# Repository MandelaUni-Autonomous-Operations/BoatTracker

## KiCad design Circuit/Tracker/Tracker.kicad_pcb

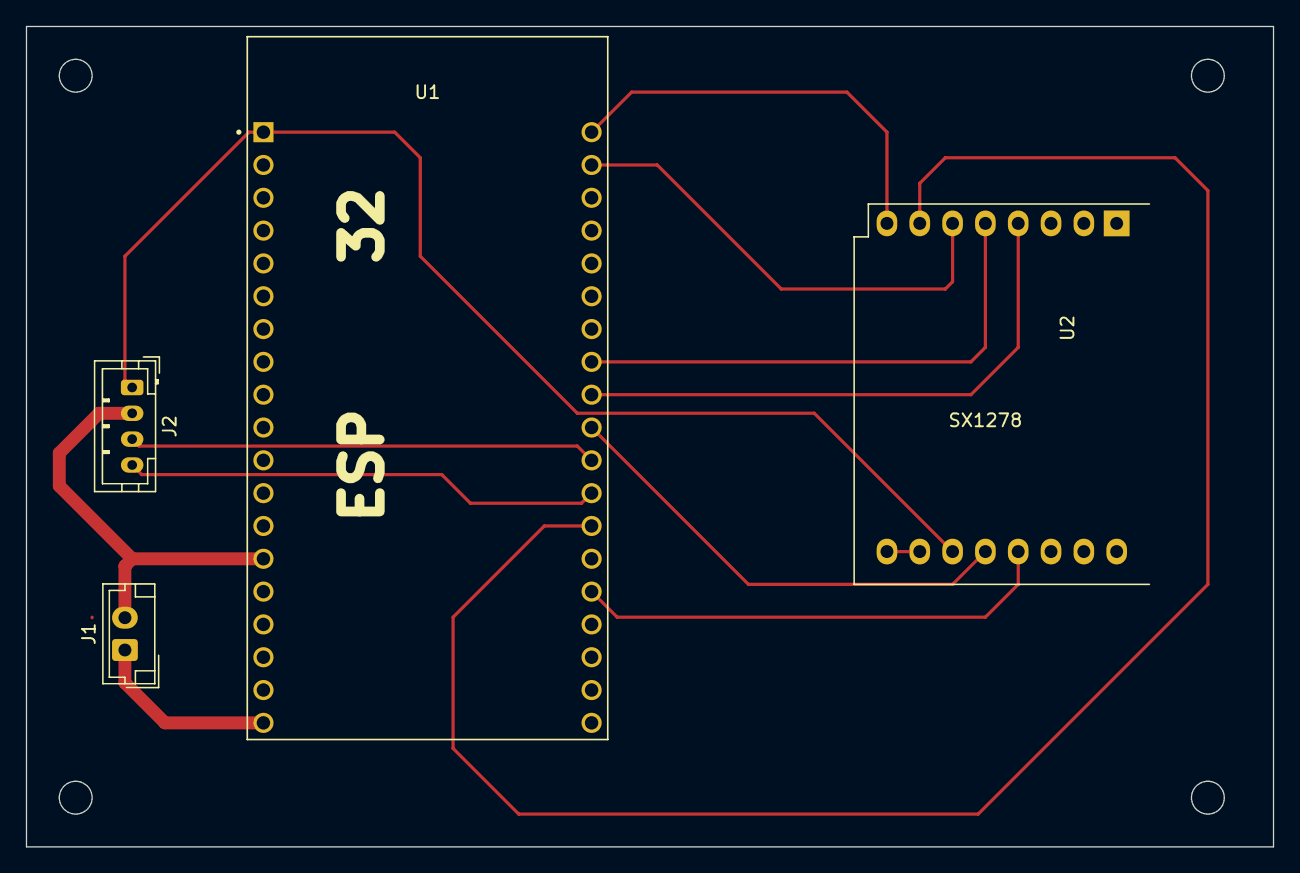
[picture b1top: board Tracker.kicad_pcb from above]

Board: 2 copper layers, 96.5 x 63.5 mm, 4 parts (0 on the bottom side), 11 nets.

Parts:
J1: Conn_01x02_Female; JST_EH_B2B-EH-A_1x02_P2.50mm_Vertical
J2: Conn_01x04_Female; JST_PH_B4B-PH-K_1x04_P2.00mm_Vertical
U1: ESP32-DEVKITC-32D; MODULE_ESP32-DEVKITC-32D
U2: SX1278; SX1276 Module

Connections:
GND: J1.2, J2.2, U1.J2-14 (GND1), U1.J3-1 (GND3), U1.J3-7 (GND2), U2.2 (VR_ANA), U2.4 (VR_DIG), U2.15 (GND)
unnamed: J1.1, U1.J2-19 (EXT_5V)
unnamed: J2.1, U1.J2-1 (3V3), U2.14 (VBAT_DIG)
unnamed: J2.3, U1.J3-11 (IO17)
unnamed: J2.4, U1.J3-12 (IO16)
unnamed: U1.J3-2 (IO23), U2.18 (MOSI)
unnamed: U1.J3-8 (IO19), U2.17 (MISO)
unnamed: U1.J3-9 (IO18), U2.16 (SCK)
unnamed: U1.J3-10 (IO5), U2.7 (~RESET)
unnamed: U1.J3-13 (IO4), U2.19 (NSS)
unnamed: U1.J3-15 (IO2), U2.8 (DIO0)
